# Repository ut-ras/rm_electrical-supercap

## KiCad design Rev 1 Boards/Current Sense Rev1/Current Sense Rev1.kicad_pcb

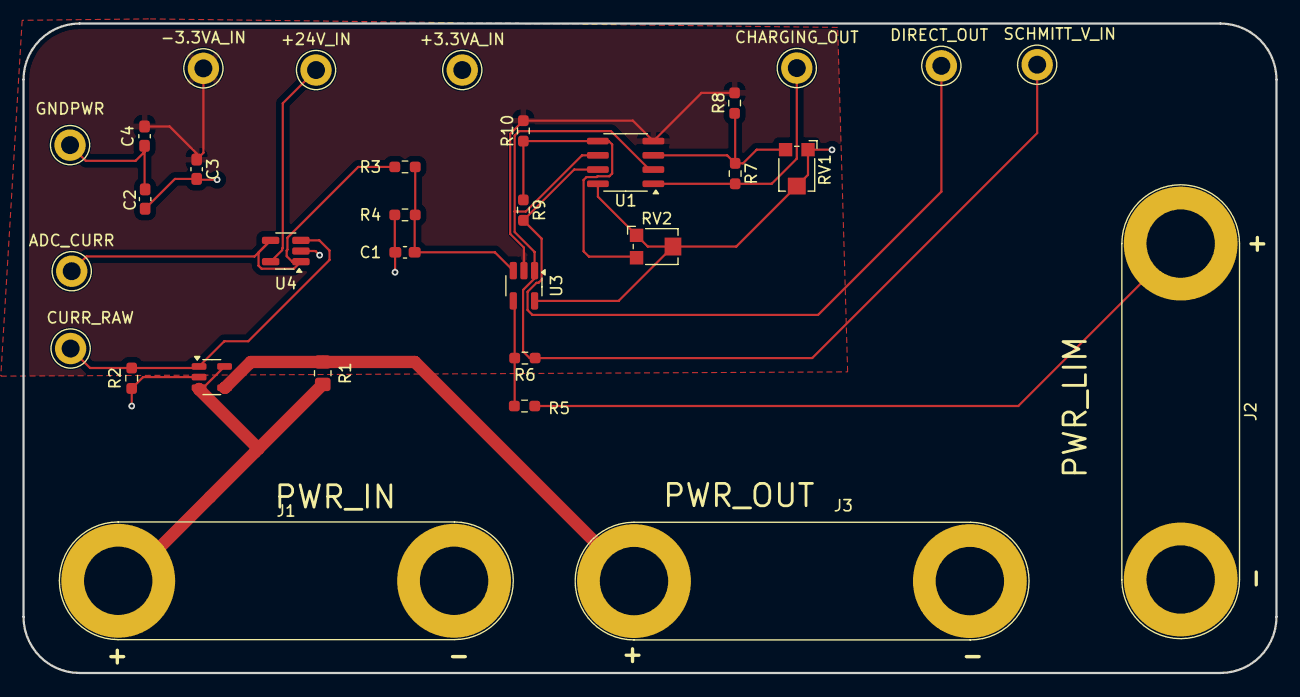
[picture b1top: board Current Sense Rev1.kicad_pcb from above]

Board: 4 copper layers, 111.8 x 57.9 mm, 32 parts (0 on the bottom side), 16 nets.

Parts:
+3.3VA_IN, +24V_IN: TestPoint; TestPoint_Keystone_5010-5014_Multipurpose
-3.3VA_IN: TestPoint; TestPoint_Keystone_5010-5014_Multipurpose
ADC_CURR: TestPoint; TestPoint_Keystone_5010-5014_Multipurpose
C1: 100p; C_0603_1608Metric_Pad1.08x0.95mm_HandSolder
C2, C3, C4: 0.1u; C_0603_1608Metric_Pad1.08x0.95mm_HandSolder
CHARGING_OUT: TestPoint; TestPoint_Keystone_5010-5014_Multipurpose
CURR_RAW: TestPoint; TestPoint_Keystone_5010-5014_Multipurpose
DIRECT_OUT: TestPoint; TestPoint_Keystone_5010-5014_Multipurpose
GNDPWR: TestPoint; TestPoint_Keystone_5010-5014_Multipurpose
J1, J2, J3: Conn_01x02_Socket; Banana_Jack_2Pin
R1: 0.02; R_0805_2012Metric_Pad1.20x1.40mm_HandSolder
R2: 100k; R_0603_1608Metric_Pad0.98x0.95mm_HandSolder
R3, R5: 30k; R_0603_1608Metric_Pad0.98x0.95mm_HandSolder
R4, R6: 120k; R_0603_1608Metric_Pad0.98x0.95mm_HandSolder
R7, R9: 12k; R_0603_1608Metric_Pad0.98x0.95mm_HandSolder
R8, R10: 1k; R_0603_1608Metric_Pad0.98x0.95mm_HandSolder
RV1, RV2: TC33X-2-302E; Potentiometer_Bourns_TC33X_Vertical
SCHMITT_V_IN: TestPoint; TestPoint_Keystone_5010-5014_Multipurpose
U1: TS3702; SOIC-8_3.9x4.9mm_P1.27mm
U2: INA138; SOT-23-5
U3, U4: TLV9301; SOT-23-5_HandSoldering

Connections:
+3.3VA: +3.3VA_IN.1, C2.2, C3.2, RV1.1, RV1.2, RV2.1, RV2.2, U1.8 (V+), U3.5 (V+)
+24V: +24V_IN.1, U4.5 (V+)
-3V3: -3.3VA_IN.1, C3.1, C4.1, R8.2, R10.2, U1.4 (V-), U3.2 (V-)
/Current Sense/CEN_REF: R7.1, R8.1, RV1.3, U1.3 (+)
/Current Sense/CHARGING_IEN: CHARGING_OUT.1, R7.2, U1.1
/Current Sense/CURR: ADC_CURR.1, R3.1, U4.1, U4.4 (-)
/Current Sense/DEN_REF: R9.1, R10.1, RV2.3, U1.5 (+)
/Current Sense/DIRECT_IEN: DIRECT_OUT.1, R9.2, U1.7
/Current Sense/POW_LIMIT: J2.1, R5.1
/Current Sense/PWR_{IN}: J1.1, R1.1, U2.3 (+), U2.5 (V+)
/Current Sense/PWR_{OUT}: J3.1, R1.2, U2.4 (-)
/Current Sense/VN: C1.2, R3.2, R4.1, U3.3 (+)
/Current Sense/VP: R5.2, R6.1, U3.4 (-)
CURR_{RAW}: CURR_RAW.1, R2.1, U2.1, U4.3 (+)
GNDPWR: C1.1, C2.1, C4.2, GNDPWR.1, J1.2, J2.2, J3.2, R2.2, R4.2, U2.2 (GND), U4.2 (V-)
V_EXTRA: R6.2, SCHMITT_V_IN.1, U1.2 (-), U1.6 (-), U3.1

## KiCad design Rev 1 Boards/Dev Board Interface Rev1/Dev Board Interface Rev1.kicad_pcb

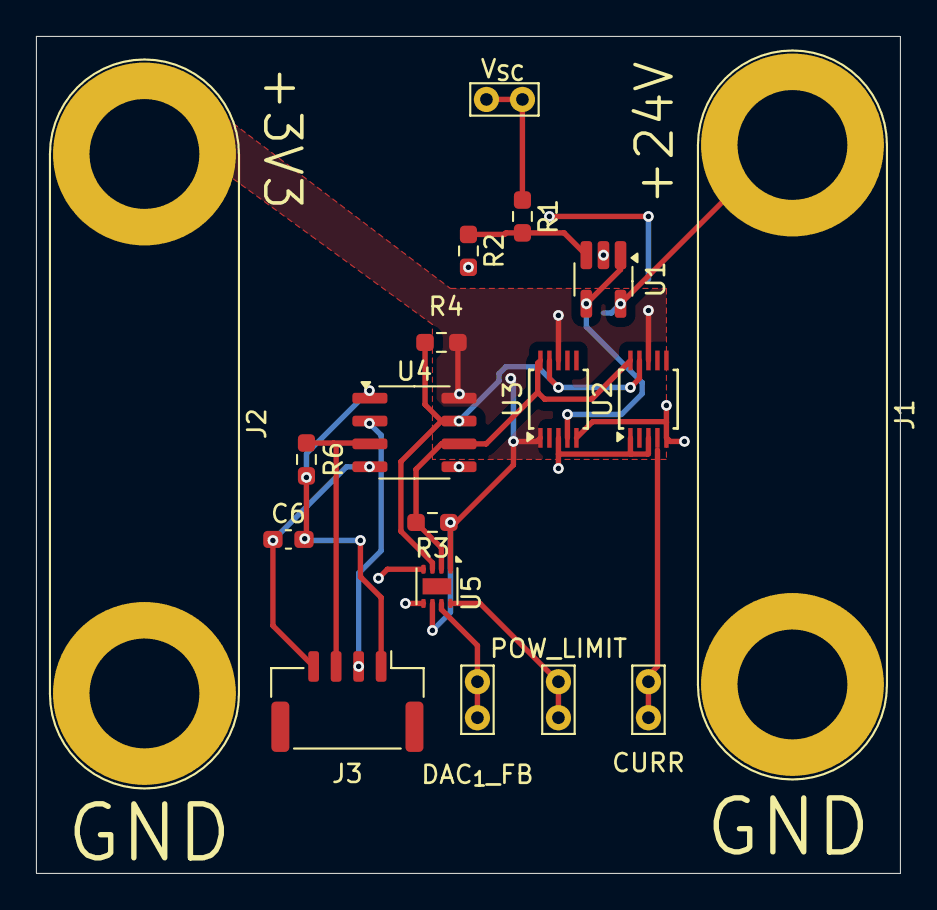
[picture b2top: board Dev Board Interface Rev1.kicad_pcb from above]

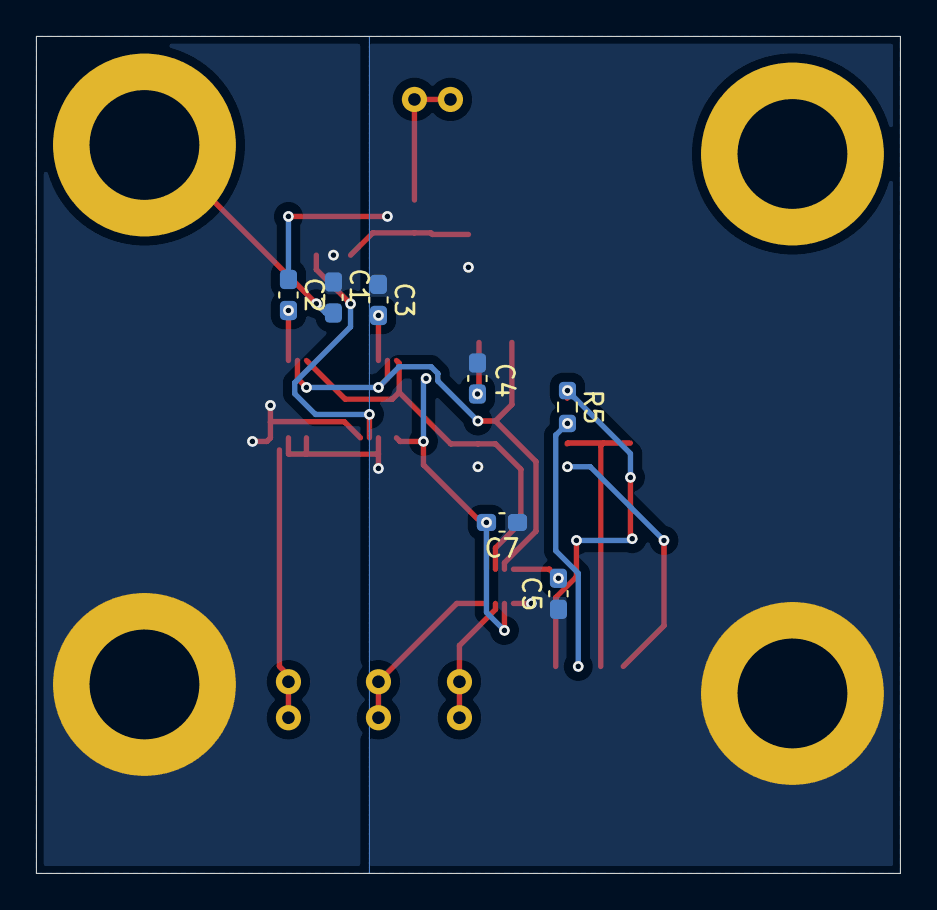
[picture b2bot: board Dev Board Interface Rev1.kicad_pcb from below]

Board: 2 copper layers, 48.0 x 46.5 mm, 25 parts (7 on the bottom side), 17 nets.

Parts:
C1, C2, C3, C4, C6, C7: 0.1u; C_0603_1608Metric_Pad1.08x0.95mm_HandSolder
C5: 6.8u; C_0603_1608Metric_Pad1.08x0.95mm_HandSolder
CURR: TestPoint; TestPoint_Bridge_Pitch2.0mm_Drill0.7mm
DAC_{1}_FB: TestPoint; TestPoint_Bridge_Pitch2.0mm_Drill0.7mm
J1, J2: Conn_01x02_Pin; Banana_Jack_2Pin
J3: Conn_01x04_Pin; JST_GH_BM04B-GHS-TBT_1x04-1MP_P1.25mm_Vertical
POW_LIMIT: TestPoint; TestPoint_Bridge_Pitch2.0mm_Drill0.7mm
R1: 180k; R_0603_1608Metric_Pad0.98x0.95mm_HandSolder
R2: 120k; R_0603_1608Metric_Pad0.98x0.95mm_HandSolder
R3, R4, R5, R6: 1.5k; R_0603_1608Metric_Pad0.98x0.95mm_HandSolder
U1: TLV9301xDBV; SOT-23-5_HandSoldering
U2, U3: ADS1014IDGS; TSSOP-10_3x3mm_P0.5mm
U4: ISO164xB; SOIC-8_3.9x4.9mm_P1.27mm
U5: DACx53401; WSON-8-1EP_2x2mm_P0.5mm_EP0.9x1.6mm
V_{SC}: TestPoint; TestPoint_Bridge_Pitch2.0mm_Drill0.7mm

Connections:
+3V3: C2.2, C3.2, C4.1, C7.2, J2.1, R3.1, R4.1, U2.8 (VDD), U3.1 (ADDR), U3.8 (VDD), U4.8 (VCC2), U5.1 (A0), U5.6 (VDD)
+24V: C1.2, J1.1, U1.5 (V+)
/+3V3_{DEV}: C6.2, J3.1, R5.1, R6.1, U4.1 (VCC1)
/CURR: CURR.1, U2.4 (AIN0)
/DAC_{1}_FB: DAC_{1}_FB.1, U5.7 (FB)
/Dev Board Interface/CAP_{1}: C5.1, U5.4 (CAP)
/Dev Board Interface/SCL_{INT}: R3.2, U2.10 (SCL), U3.10 (SCL), U4.6 (SCL2), U5.2 (SCL)
/Dev Board Interface/SDA_{INT}: R4.2, U2.9 (SDA), U3.9 (SDA), U4.7 (SDA2), U5.3 (SDA)
/Dev Board Interface/V_{SC}_BUF: U1.1, U1.4 (-), U3.4 (AIN0)
/Dev Board Interface/V_{SC}_scaled: R1.2, R2.1, U1.3 (+)
/POW_LIMIT: POW_LIMIT.1, U5.8 (OUT)
/SCL_{IN}: J3.3, R6.2, U4.3 (SCL1)
/SDA_{IN}: J3.2, R5.2, U4.2 (SDA1)
/V_{SC}: R1.1, V_{SC}.1
GND: C2.1, C3.1, C4.2, C5.2, C7.1, J2.2, R2.2, U2.1 (ADDR), U2.3 (GND), U3.3 (GND), U4.5 (GND2), U5.5 (AGND)
GNDD: C6.1, J3.4, U4.4 (GND1)
GNDPWR: C1.1, J1.2, U1.2 (V-), U2.5 (AIN1), U3.5 (AIN1)

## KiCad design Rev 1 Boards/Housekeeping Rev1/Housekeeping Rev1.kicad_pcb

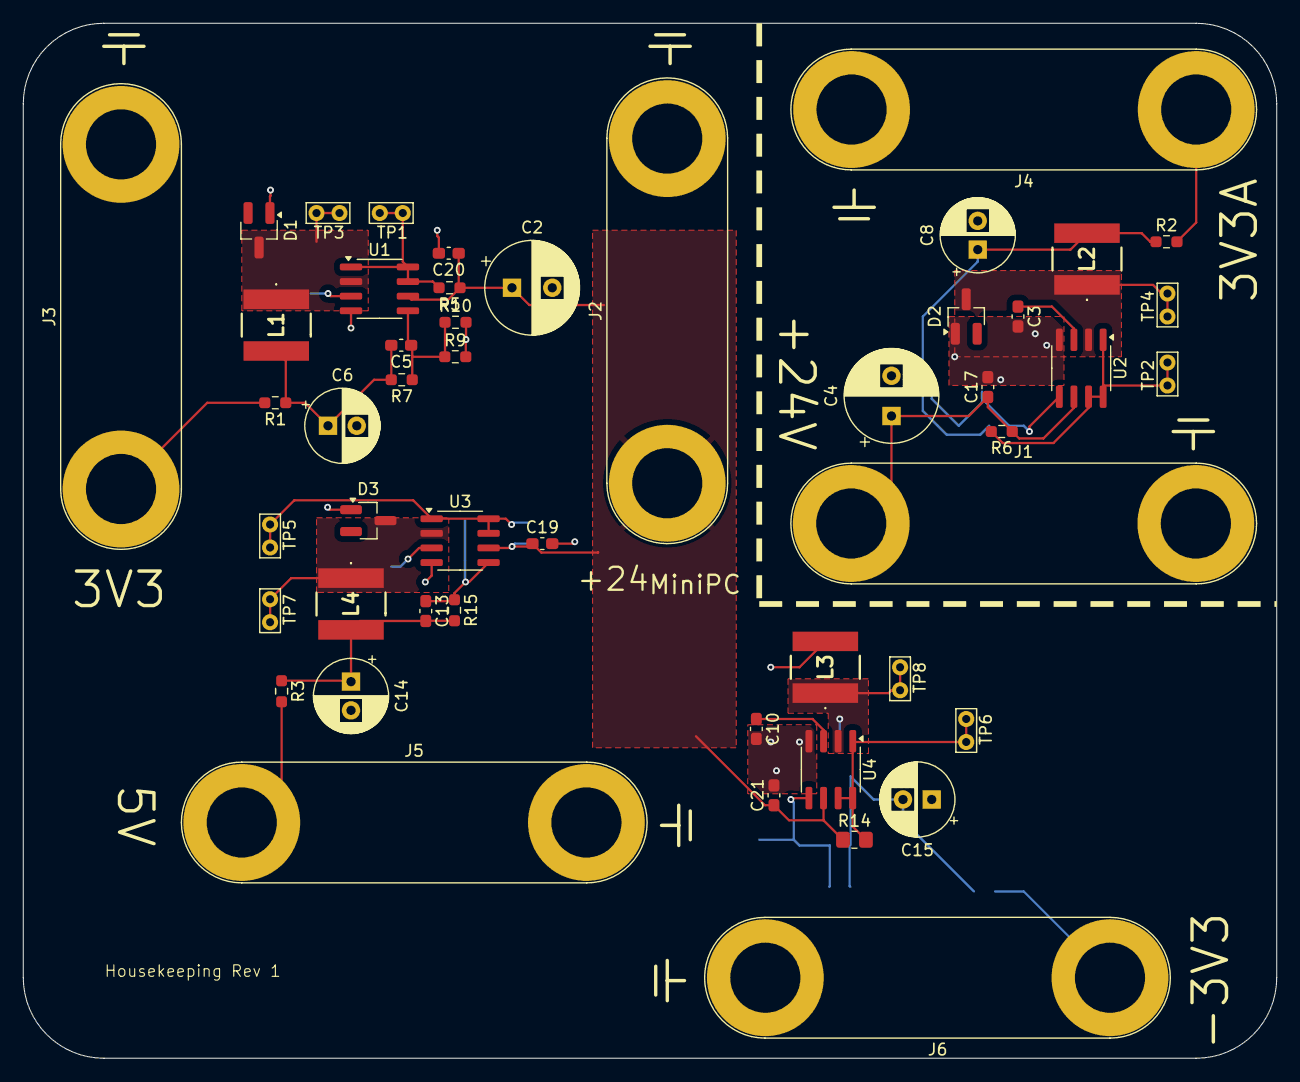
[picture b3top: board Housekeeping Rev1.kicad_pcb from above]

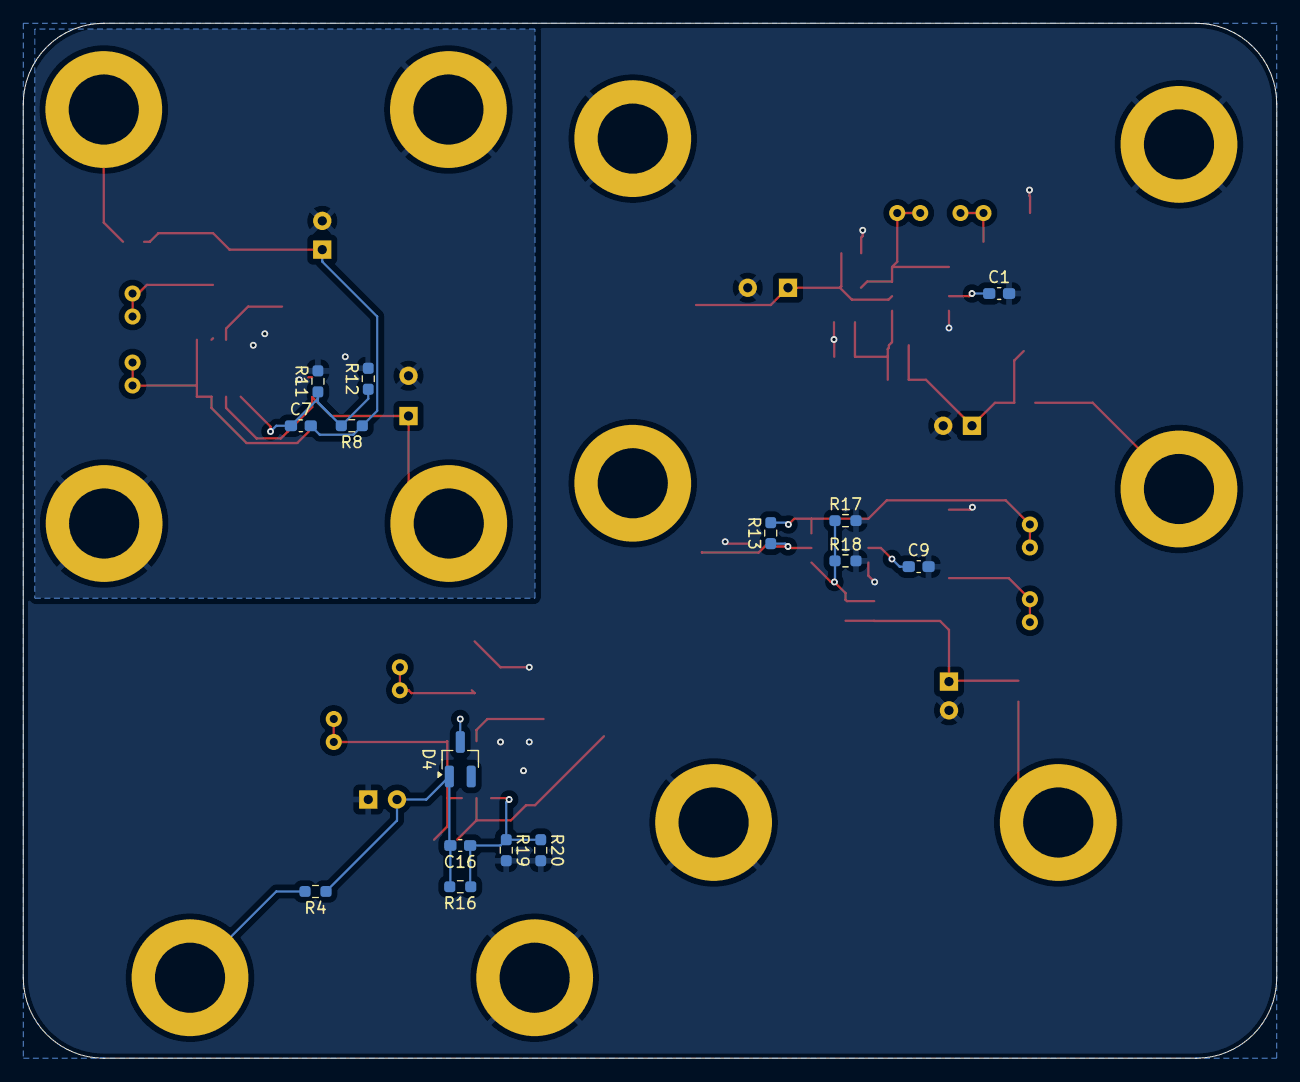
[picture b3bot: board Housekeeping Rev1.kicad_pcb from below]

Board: 2 copper layers, 109.0 x 90.0 mm, 64 parts (15 on the bottom side), 28 nets.

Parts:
C1, C3: 75p; C_0603_1608Metric_Pad1.08x0.95mm_HandSolder
C2, C4: 100u; CP_Radial_D8.0mm_P3.50mm
C5, C7, C13, C16: 0.01u; C_0603_1608Metric_Pad1.08x0.95mm_HandSolder
C6, C8, C14, C15: 470u; CP_Radial_D6.3mm_P2.50mm
C9: 100p; C_0603_1608Metric_Pad1.08x0.95mm_HandSolder
C10: 68p; C_0603_1608Metric_Pad1.08x0.95mm_HandSolder
C17, C19, C20, C21: 1u; C_0603_1608Metric_Pad1.08x0.95mm_HandSolder
D1, D2, D3, D4: BAT54; SOT-23_Handsoldering
J1, J2, J3, J4, J5, J6: Conn_01x02_Socket; Banana_Jack_2Pin
L1, L2, L4: 220u; ASPIAIGS6055221MT
L3: 88u; ASPIAIGS6055221MT
R1, R2, R3, R4: 50; R_0603_1608Metric_Pad0.98x0.95mm_HandSolder
R5, R6, R13: 1; R_0603_1608Metric_Pad0.98x0.95mm_HandSolder
R7, R8, R16: 1.2k; R_0603_1608Metric_Pad0.98x0.95mm_HandSolder
R9, R11, R19: 6.8k; R_0603_1608Metric_Pad0.98x0.95mm_HandSolder
R10, R12, R20: 820; R_0603_1608Metric_Pad0.98x0.95mm_HandSolder
R14: 0.866; R_0805_2012Metric_Pad1.20x1.40mm_HandSolder
R15: 4.7k; R_0603_1608Metric_Pad0.98x0.95mm_HandSolder
R17: 12k; R_0603_1608Metric_Pad0.98x0.95mm_HandSolder
R18: 1.8k; R_0603_1608Metric_Pad0.98x0.95mm_HandSolder
TP1, TP2, TP5, TP6: V_{C}; TestPoint_Bridge_Pitch2.0mm_Drill0.7mm
TP3, TP4, TP7, TP8: V_{E}; TestPoint_Bridge_Pitch2.0mm_Drill0.7mm
U1, U2, U3, U4: MC34063A; SOIC-8_3.9x4.9mm_P1.27mm

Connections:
+3.3VA: C7.2, C8.1, L2.2, R2.1, R8.1
+3V3: C5.2, C6.1, L1.2, R1.1, R7.2
+5V: C13.2, C14.1, L4.2, R3.1, R15.2
+24V: C4.1, C17.1, J1.1, R6.1, U2.6 (VCC)
-3V3: C15.2, C16.2, D4.1 (A), R4.1, R16.2
/3V3AbR: J4.1, R2.2
/3V3bR: J3.1, R1.2
/5VbR: J5.1, R3.2
/+24_{MiniPC}: C2.1, C19.1, C20.1, C21.1, J2.1, R5.1, R13.1, R14.1, U1.6 (VCC), U3.6 (VCC), U4.6 (VCC)
/-3V3bR: J6.1, R4.2
/Housekeeping Power Supplies/3V3A_COMP: C7.1, R8.2, R11.1, R12.1, U2.5 (COMP-)
/Housekeeping Power Supplies/3V3A_CT: C3.1, U2.3 (CT)
/Housekeeping Power Supplies/3V3A_SW: D2.3 (K), L2.1, TP4.1, U2.2 (SE)
/Housekeeping Power Supplies/3V3A_VC: R6.2, TP2.1, U2.1 (SC), U2.7 (I_{PK}), U2.8 (DC)
/Housekeeping Power Supplies/3V3_COMP: C5.1, R7.1, R9.1, R10.1, U1.5 (COMP-)
/Housekeeping Power Supplies/3V3_CT: C1.1, U1.3 (CT)
/Housekeeping Power Supplies/3V3_SW: D1.3 (K), L1.1, TP3.1, U1.2 (SE)
/Housekeeping Power Supplies/3V3_VC: R5.2, TP1.1, U1.1 (SC), U1.7 (I_{PK}), U1.8 (DC)
/Housekeeping Power Supplies/5V_COMP: C13.1, R15.1, R17.1, R18.1, U3.5 (COMP-)
/Housekeeping Power Supplies/5V_CT: C9.1, U3.3 (CT)
/Housekeeping Power Supplies/5V_SW: D3.3 (K), L4.1, TP7.1, U3.2 (SE)
/Housekeeping Power Supplies/5V_VC: R13.2, TP5.1, U3.1 (SC), U3.7 (I_{PK}), U3.8 (DC)
/Housekeeping Power Supplies/-3V3_COMP: C16.1, R16.1, R19.1, R20.1, U4.5 (COMP-)
/Housekeeping Power Supplies/-3V3_CT: C10.1, U4.3 (CT)
/Housekeeping Power Supplies/-3V3_SW: D4.3 (K), L3.1, TP8.1, U4.2 (SE)
/Housekeeping Power Supplies/-3V3_VC: R14.2, TP6.1, U4.1 (SC), U4.7 (I_{PK}), U4.8 (DC)
GND: C1.2, C2.2, C6.2, C9.2, C10.2, C14.2, C15.1, C19.2, C20.2, C21.2, D1.1 (A), D3.1 (A), J2.2, J3.2, J5.2, J6.2, L3.2, R9.2, R10.2, R17.2, R18.2, R19.2, R20.2, U1.4 (GND), U3.4 (GND), U4.4 (GND)
GNDPWR: C3.2, C4.2, C8.2, C17.2, D2.1 (A), J1.2, J4.2, R11.2, R12.2, U2.4 (GND)

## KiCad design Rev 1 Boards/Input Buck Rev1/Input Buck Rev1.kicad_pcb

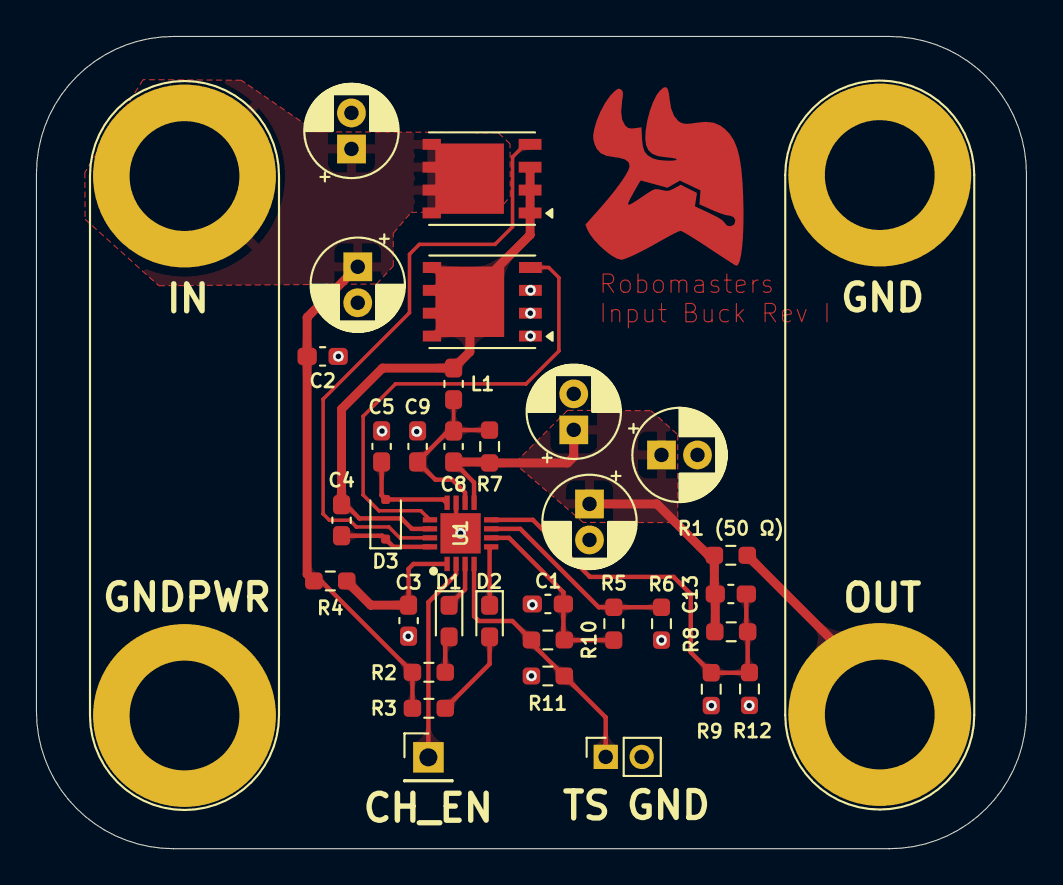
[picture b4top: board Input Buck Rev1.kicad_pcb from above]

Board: 2 copper layers, 55.0 x 45.1 mm, 36 parts (0 on the bottom side), 20 nets.

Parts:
C1, C3, C5: 1u; C_0603_1608Metric_Pad1.08x0.95mm_HandSolder
C2: 2.2u; C_0603_1608Metric_Pad1.08x0.95mm_HandSolder
C4, C8, C9: 0.1u; C_0603_1608Metric_Pad1.08x0.95mm_HandSolder
C6, C7, C10, C11, C12: 10u; CP_Radial_D5.0mm_P2.00mm
C13: 1.3p; C_0603_1608Metric_Pad1.08x0.95mm_HandSolder
D1: LTST-C193TBKT-5A; LED_0603_1608Metric_Pad1.05x0.95mm_HandSolder
D2: LTST-C193KSKT-5A; LED_0603_1608Metric_Pad1.05x0.95mm_HandSolder
D3: BAT54J; D_SOD-323F
J1, J2: Conn_01x02_Socket; Banana_Jack_2Pin
J3: Conn_01x01_Pin; PinHeader_1x01_P2.54mm_Vertical
J4: Conn_01x02_Socket; PinSocket_1x02_P2.00mm_Vertical
L1: 4.7u; L_0603_1608Metric_Pad1.05x0.95mm_HandSolder
Q1, Q2: RS1G120MNTB; PowerPAK_SO-8_Single
R1 (50 Ω): 50; R_0603_1608Metric_Pad0.98x0.95mm_HandSolder
R2, R3: 4.7k; R_0603_1608Metric_Pad0.98x0.95mm_HandSolder
R4: 6.8; R_0603_1608Metric_Pad0.98x0.95mm_HandSolder
R5: 75k; R_0603_1608Metric_Pad0.98x0.95mm_HandSolder
R6: 24k; R_0603_1608Metric_Pad0.98x0.95mm_HandSolder
R7: 10m; R_0603_1608Metric_Pad0.98x0.95mm_HandSolder
R8: 200k; R_0603_1608Metric_Pad0.98x0.95mm_HandSolder
R9: 280k; R_0603_1608Metric_Pad0.98x0.95mm_HandSolder
R10: 2.74k; R_0603_1608Metric_Pad0.98x0.95mm_HandSolder
R11: 9.53k; R_0603_1608Metric_Pad0.98x0.95mm_HandSolder
R12: 1.05Meg; R_0603_1608Metric_Pad0.98x0.95mm_HandSolder
U1: BQ24640; QFN50P350X350X100-17N-D

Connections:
/Input Buck/BTST: C4.1, D3.1 (K), U1.16 (BTST)
/Input Buck/CHARGE_EN: J3.1, U1.2 (CE)
/Input Buck/HIDRV: Q1.4 (G), U1.15 (HIDRV)
/Input Buck/IN: C2.1, C6.1, C7.1, J2.2, Q1.5 (D), R2.1, R3.1, R4.1
/Input Buck/ISET: R5.2, R6.1, U1.7 (ISET)
/Input Buck/LODRV: Q2.4 (G), U1.13 (LODRV)
/Input Buck/PH: C4.2, L1.1, Q1.1 (S), Q1.2 (S), Q1.3 (S), Q2.5 (D), U1.14 (PH)
/Input Buck/REGN: C5.1, D3.2 (A), U1.12 (REGN)
/Input Buck/SRN: C8.2, C10.1, C11.1, C12.1, C13.1, R1 (50 Ω).2, R7.1, R8.1, U1.9 (SRN)
/Input Buck/SRP: C8.1, C9.1, L1.2, R7.2, U1.10 (SRP)
/Input Buck/STAT: D1.1 (K), U1.3 (STAT)
/Input Buck/STAT_D: D1.2 (A), R2.2
/Input Buck/TS: J4.1, R10.2, R11.1, U1.4 (TS)
/Input Buck/VCC: C3.1, R4.2, U1.1 (VCC)
/Input Buck/VFB: C13.2, R8.2, R9.1, R12.1, U1.8 (VFB)
/Input Buck/VREF: C1.1, R5.1, R10.1, U1.6 (VREF)
/Input Buck/~PG: D2.1 (K), U1.5 (~PG)
/Input Buck/~PG_D: D2.2 (A), R3.2
/out: J1.2, R1 (50 Ω).1
GNDPWR: C1.2, C2.2, C3.2, C5.2, C6.2, C7.2, C9.2, C10.2, C11.2, C12.2, J2.1, J4.2, Q2.1 (S), Q2.2 (S), Q2.3 (S), R6.2, R9.2, R11.2, R12.2, U1.11 (GND), U1.17 (PAD)
